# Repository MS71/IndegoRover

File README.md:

# IndegoRover
new MainBoard for Indego Lawn Mower

Prototype:

Schematic:
https://github.com/MS71/IndegoRover/blob/main/kicad/IndegoMower/pdf/IndegoMower.pdf

PCB:

Parts:
* ESP32 (S2/S3) Module (https://github.com/MS71/ROS2Mower/blob/master/hw/esp32_module.pdf)
* ARV Mega 128 for low level IO, security and motor driver
* origonal Indego connectors (26SHC-B-1A => mouser)
* DC motor driver: 3 * VNH2SP30 module (41V, 30A H Bridge)
* GPS receiver (ZED-F9P) (https://www.ardusimple.com/product/simplertk2blite/)
* 5 pin header for low cost, non RTK GPS receiver
* 10 Pin RPI Connector (5V, 3.3V, GND, I2C, UART)
* 10 Pin I2C Bus Connector
* 6 Pin I2C Bus Connector
* 5V Step Down Converter
* Bat Charger Circuit (Compatible with Indego Charge Station, difficult)
* Bat Charger Circuit (Compatible with std. 36V solar panel)
* Coil Sensor Amp
* low power + standby
* support for all available sensors
* BNO055 IMU module headers
* support for all sensors (bumper, coil fensem ...)
* power supply for onboard computer
* beeper
* support for LCD and keyboard (difficult)
* some breadboard area for custom extensions
* ...

onboard ROS2 computer: (optional)
* RPI4 or RPI Zero 2W headers 
* Orange Pi Zero 2 headers (http://www.orangepi.org/Orange%20Pi%20Zero2/)
* ...

Other:
* made with free Eagle  (max. 80 qcm) or kicad6

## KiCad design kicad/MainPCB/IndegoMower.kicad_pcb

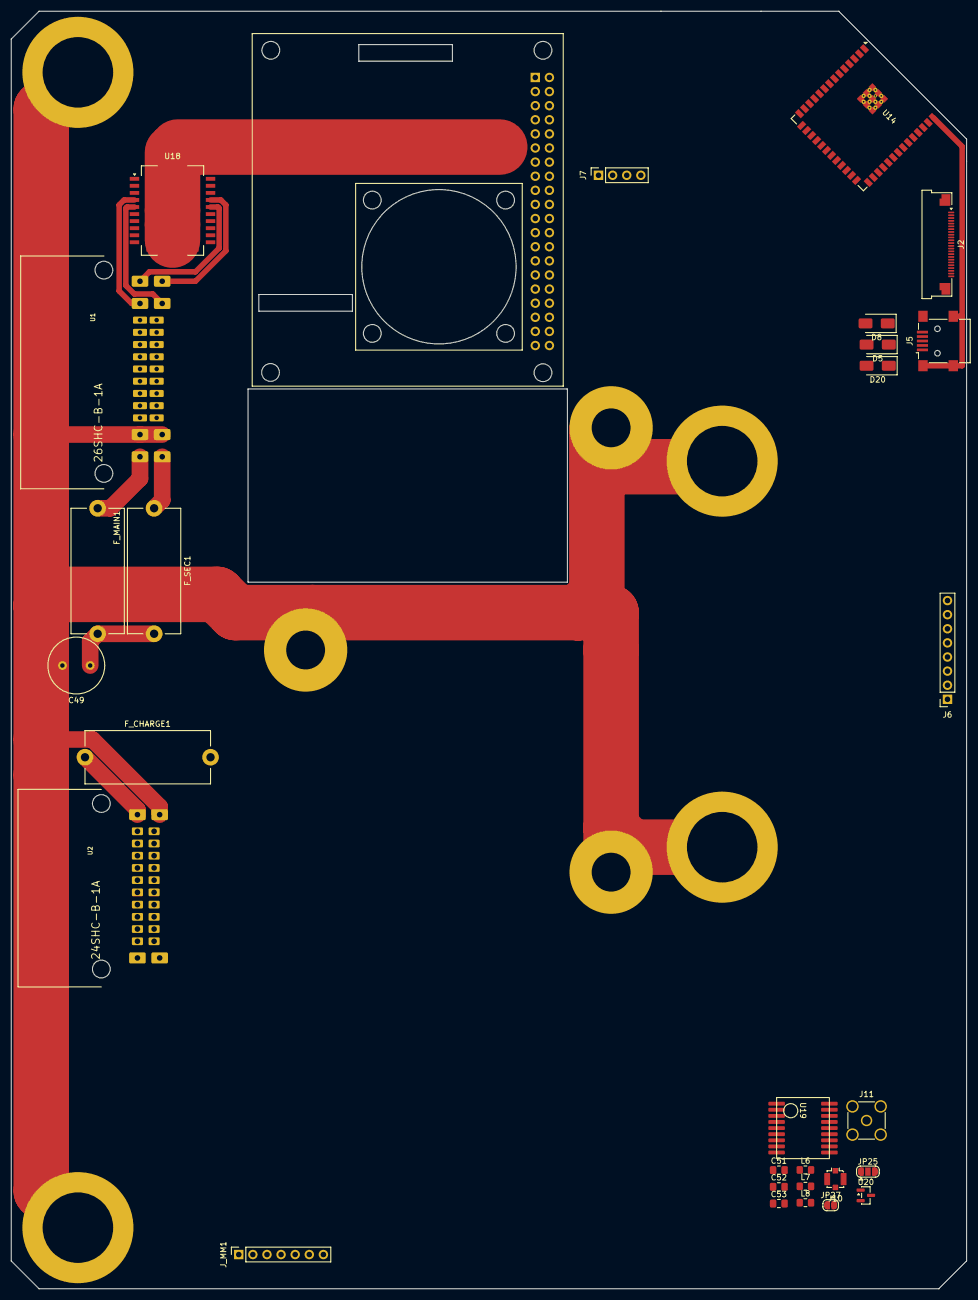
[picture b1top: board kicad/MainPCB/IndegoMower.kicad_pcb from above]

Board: 2 copper layers, 172.0 x 230.0 mm, 29 parts (1 on the bottom side), 38 nets.

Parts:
C49: 680uF / 63V; C_Radial_D10.0mm_H16.0mm_P5.00mm
C51, C52, C53: 100nF; C_0805_2012Metric_Pad1.18x1.45mm_HandSolder
D5, D8, D20: P4SMAJ5.0CA; D_SMA
F_CHARGE1: 4A; Fuseholder_Cylinder-5x20mm_Stelvio-Kontek_PTF78_Horizontal_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
F_MAIN1: 6A; Fuseholder_Cylinder-5x20mm_Stelvio-Kontek_PTF78_Horizontal_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
F_SEC1: 6A; Fuseholder_Cylinder-5x20mm_Stelvio-Kontek_PTF78_Horizontal_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
J1: RPi_GPIO; PinSocket_2x20_P2.54mm_Vertical
J2: Conn_01x24_FFC_0.5mm_AFC01-S24FCC-00; Amphenol_F32R-1A7x1-11024_1x24-1MP_P0.5mm_Horizontal
J5: USB_OTG; USB_Mini-B_Lumberg_2486_01_Horizontal
J6: BNO055; PinSocket_1x08_P2.54mm_Vertical
J7: OLED; PinSocket_1x04_P2.54mm_Vertical
J10: IPEX; U.FL_Molex_MCRF_73412-0110_Vertical
J11: SMA; SMA_Amphenol_132134-11_Vertical
JP25: SolderJumper_3_Open; SolderJumper-3_P1.3mm_Open_RoundedPad1.0x1.5mm
JP27: SolderJumper_2_Open; SolderJumper-2_P1.3mm_Open_RoundedPad1.0x1.5mm
J_MM1: PinSocket_1x07_P2.54mm_Vertical
L6: 1.2uH; L_0805_2012Metric_Pad1.15x1.40mm_HandSolder
L7, L8: 39nH; L_0805_2012Metric_Pad1.15x1.40mm_HandSolder
U1: 26SHC-B-1A
U2: 24SHC-B-1A
U14: ESP32-S3-WROOM-2 (-1); ESP32-S3-WROOM-2
U18: L298P; HSOP-20-1EP_11.0x15.9mm_P1.27mm_SlugDown
U19: RTK-1010; rtk1010
U20: MCP1700-3302E_SOT23; SOT-23

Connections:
+2V8: J2.14, J2.21
+3.3V: J_MM1.7, U18.12 (Vss)
CAM_D0: J2.6, U14.23 (GPIO21)
CAM_D1: J2.4, U14.39 (GPIO1/TOUCH1/ADC1_CH0)
CAM_D2: J2.3, U14.38 (GPIO2/TOUCH2/ADC1_CH1)
CAM_D3: J2.5, U14.35 (MTMS/GPIO42)
CAM_D4: J2.7, U14.34 (MTDI/GPIO41/CLK_OUT1)
CAM_D5: J2.9, U14.33 (MTDO/GPIO40/CLK_OUT2)
CAM_D6: J2.11, U14.32 (MTCK/GPIO39/CLK_OUT3/SUBSPICS1)
CAM_D7: J2.13, U14.31 (GPIO38/FSPIWP/SUBSPIWP)
CAM_HREF: J2.16, U14.25 (GPIO48/SPICLK_N/SUBSPICLK_N_DIFF)
CAM_PCLK: J2.8, U14.26 (GPIO45)
CAM_SDA: J2.22, U14.4 (GPIO4/TOUCH4/ADC1_CH3)
CAM_XCLK: J2.12, U14.16 (GPIO46)
GND: C51.2, C52.2, C53.2, J2.10, J2.23, J10.2 (Ext), J11.2 (Ext), U19.1 (GND1), U19.10 (GND10), U19.12 (GND12), U20.1 (GND)
GNDD: C49.2, D5.2 (A2), D8.2 (A2), D20.2 (A2), J5.5 (GND), J5.6 (Shield), J_MM1.6, U1.P$8, U1.P$14, U1.P$24, U1.P$25, U2.P$3, U2.P$21, U14.1 (GND), U14.40 (GND), U14.41 (GND)
GNDPWR: J1.6 (GND), J1.9 (GND), J1.14 (GND), J1.20 (GND), J1.25 (GND), J1.30 (GND), J1.34 (GND), J1.39 (GND), U18.1 (GND), U18.10 (GND), U18.11 (GND), U18.20 (GND)
ML_N: U1.P$5, U18.5 (OUT2)
ML_P: U1.P$4, U18.4 (OUT1)
MR_N: U1.P$3, U18.17 (OUT4)
MR_P: U1.P$2, U18.16 (OUT3)
unnamed: D5.1 (A1), J5.2 (D-)
unnamed: D8.1 (A1), J5.3 (D+)
unnamed: D20.1 (A1), J5.4 (ID)
unnamed: J10.1 (In), J11.1 (In), L7.2, L8.2, U19.11 (RF_IN)
unnamed: C51.1, JP25.1 (A), JP27.1 (A), L6.2, U19.8 (VCC)
unnamed: JP25.2 (C), U19.6 (V_BKUP)
unnamed: JP27.2 (B), U19.7 (NC7)
unnamed: F_MAIN1.1, U1.P$26
unnamed: F_SEC1.1, U1.P$27
unnamed: F_CHARGE1.1, U2.P$2
unnamed: L8.1, U19.14 (VCC_RF)
U5: C52.1, U20.3 (VI)
U5SW: U1.P$9, U1.P$15, U2.P$20
UB: C49.1, F_MAIN1.2, F_SEC1.2
ULNA: C53.1, L7.1, U20.2 (VO)
U_55: J1.2 (5V), J1.4 (5V)
VCC_STBY: JP25.3 (B), U14.2 (3V3)

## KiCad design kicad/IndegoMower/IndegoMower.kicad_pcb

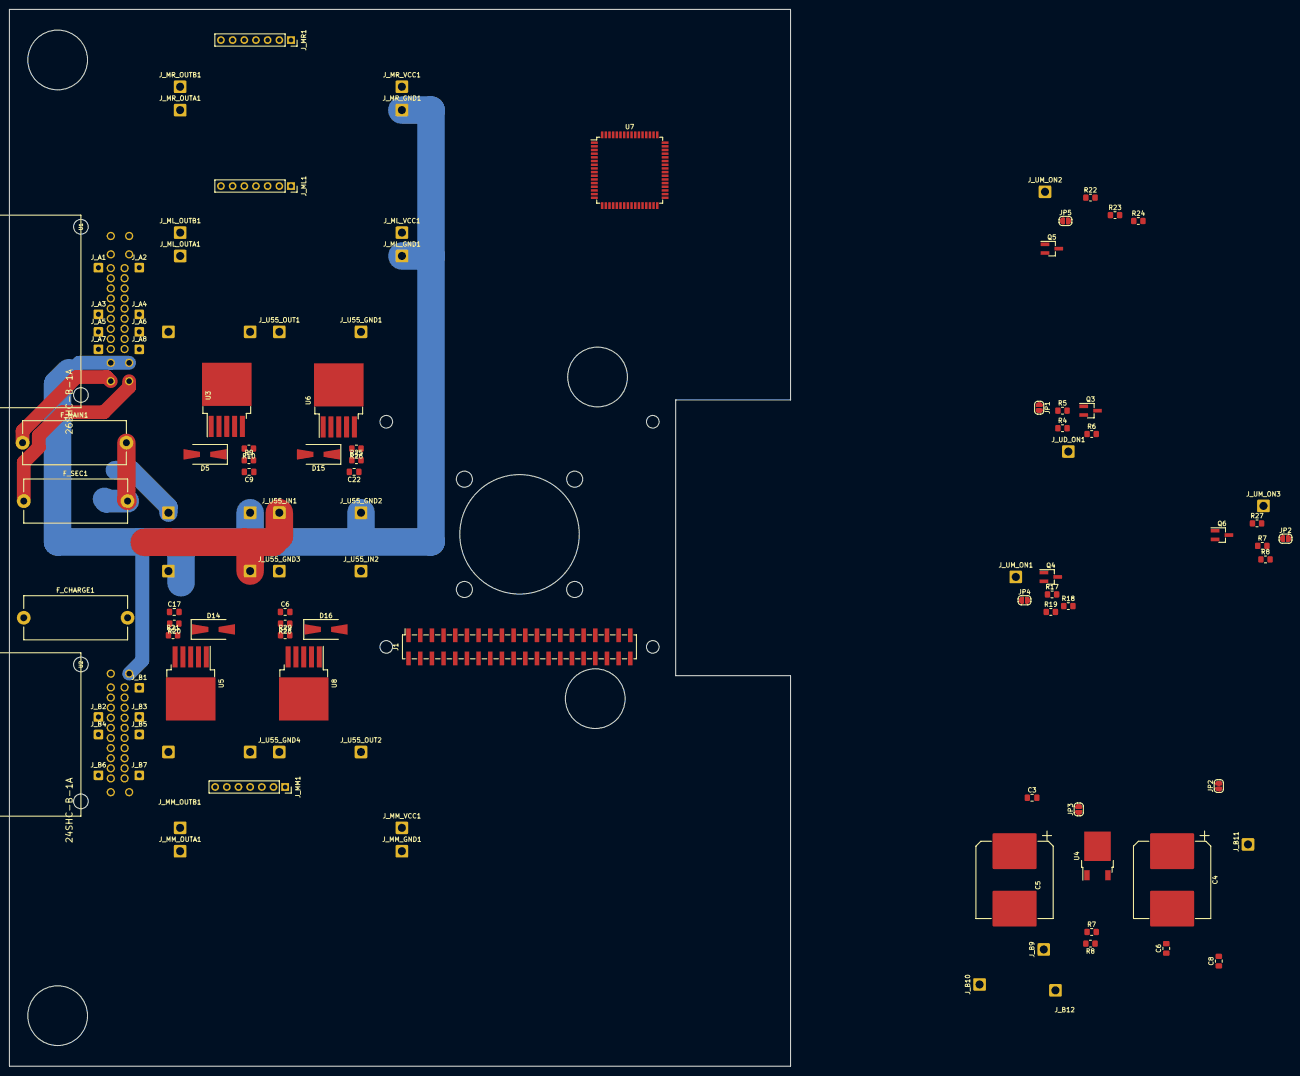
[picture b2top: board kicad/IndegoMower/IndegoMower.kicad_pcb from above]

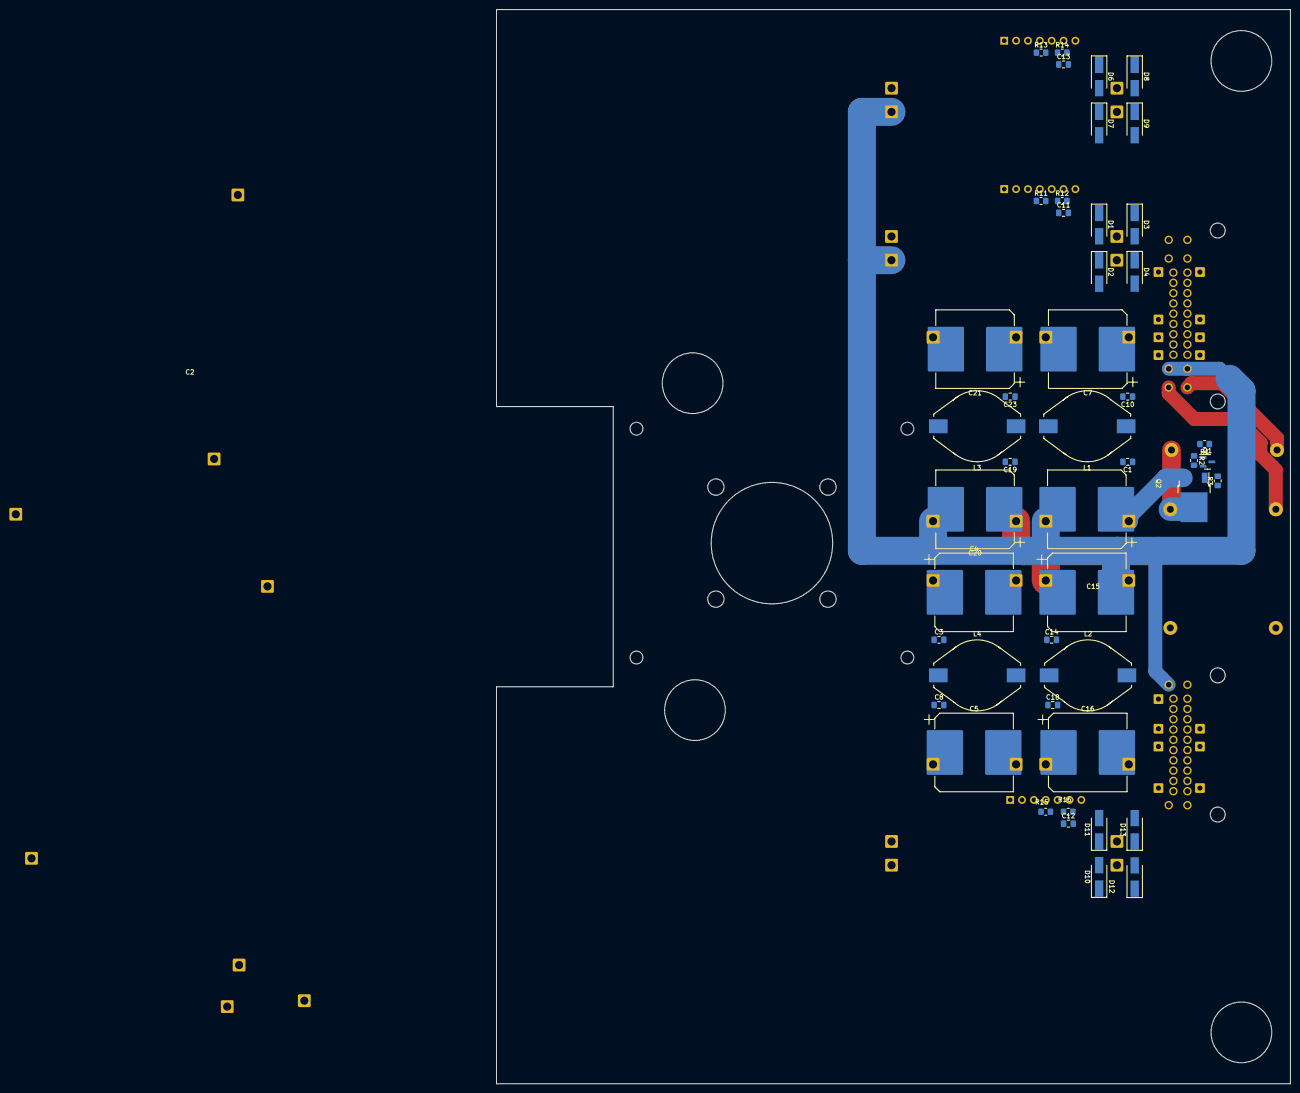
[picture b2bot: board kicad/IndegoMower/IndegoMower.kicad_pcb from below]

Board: 2 copper layers, 170.0 x 230.0 mm, 157 parts (46 on the bottom side), 61 nets.

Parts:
C1, C3, C6, C8, C10: 0.1; C_0805_2012Metric_Pad1.18x1.45mm_HandSolder
C2: 680uF/50V; CP_Elec_16x17.5
C3#2, C6#2, C8#2, C11, C12, C13, C14, C17, C18, C19, C22, C23: C_0805_2012Metric_Pad1.18x1.45mm_HandSolder
C4, C4#2, C5, C5#2, C15, C16, C20, C21: CP_Elec_16x17.5
C7: 220uF/40V; CP_Elec_16x17.5
C9: 560pF; C_0805_2012Metric_Pad1.18x1.45mm_HandSolder
D1, D2, D3, D4, D6, D7, D8, D9, D10, D11, D12, D13: D_SMA_Handsoldering
D5, D14, D15, D16: D_SMA-SMB_Universal_Handsoldering
F_CHARGE1: 4A; Fuseholder_Cylinder-5x20mm_Stelvio-Kontek_PTF78_Horizontal_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
F_MAIN1: 6A; Fuseholder_Cylinder-5x20mm_Stelvio-Kontek_PTF78_Horizontal_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
F_SEC1: 6A; Fuseholder_Cylinder-5x20mm_Stelvio-Kontek_PTF78_Horizontal_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
J1: RPi_GPIO; PinSocket_2x20_P2.54mm_Vertical_SMD
JP1, JP2#2: SolderJumper_2_Open; SolderJumper-2_P1.3mm_Open_RoundedPad1.0x1.5mm
JP2, JP3, JP4, JP5: SolderJumper-2_P1.3mm_Open_RoundedPad1.0x1.5mm
J_A1: Conn_01x01_Female; SolderWire-0.5sqmm_1x01_D0.9mm_OD2.1mm
J_A2, J_A3, J_A4, J_A5, J_A6, J_A7, J_A8: SolderWire-0.5sqmm_1x01_D0.9mm_OD2.1mm
J_B1, J_B2, J_B3, J_B4, J_B5, J_B6, J_B7: SolderWire-0.5sqmm_1x01_D0.9mm_OD2.1mm
J_B9, J_B10, J_B11, J_B12: SolderWire-1sqmm_1x01_D1.4mm_OD2.7mm
J_ML1: Conn_01x07; PinSocket_1x07_P2.54mm_Vertical
J_ML_GND1: SolderWire-1sqmm_1x01_D1.4mm_OD2.7mm
J_ML_OUTA1: SolderWire-1sqmm_1x01_D1.4mm_OD2.7mm
J_ML_OUTB1: SolderWire-1sqmm_1x01_D1.4mm_OD2.7mm
J_ML_VCC1: SolderWire-1sqmm_1x01_D1.4mm_OD2.7mm
J_MM1: PinSocket_1x07_P2.54mm_Vertical
J_MM_GND1: SolderWire-1sqmm_1x01_D1.4mm_OD2.7mm
J_MM_OUTA1: SolderWire-1sqmm_1x01_D1.4mm_OD2.7mm
J_MM_OUTB1: SolderWire-1sqmm_1x01_D1.4mm_OD2.7mm
J_MM_VCC1: SolderWire-1sqmm_1x01_D1.4mm_OD2.7mm
J_MR1: PinSocket_1x07_P2.54mm_Vertical
J_MR_GND1: SolderWire-1sqmm_1x01_D1.4mm_OD2.7mm
J_MR_OUTA1: SolderWire-1sqmm_1x01_D1.4mm_OD2.7mm
J_MR_OUTB1: SolderWire-1sqmm_1x01_D1.4mm_OD2.7mm
J_MR_VCC1: SolderWire-1sqmm_1x01_D1.4mm_OD2.7mm
J_U55_GND1, J_U55_GND2, J_U55_GND3, J_U55_GND4, J_U55_IN1, J_U55_IN2, J_U55_OUT1, J_U55_OUT2: SolderWire-1sqmm_1x01_D1.4mm_OD2.7mm
J_UD_GND1, J_UD_GND2: SolderWire-1sqmm_1x01_D1.4mm_OD2.7mm
J_UD_IN1: SolderWire-1sqmm_1x01_D1.4mm_OD2.7mm
J_UD_ON1: SolderWire-1sqmm_1x01_D1.4mm_OD2.7mm
J_UD_OUT1: SolderWire-1sqmm_1x01_D1.4mm_OD2.7mm
J_UM_GND1, J_UM_GND2: SolderWire-1sqmm_1x01_D1.4mm_OD2.7mm
J_UM_IN1: SolderWire-1sqmm_1x01_D1.4mm_OD2.7mm
J_UM_ON1, J_UM_ON2, J_UM_ON3: SolderWire-1sqmm_1x01_D1.4mm_OD2.7mm
J_UM_OUT1: SolderWire-1sqmm_1x01_D1.4mm_OD2.7mm
L1, L2, L3, L4: 33uH; L_Fastron_PISR_Handsoldering
Q1: BC847; SOT-23
Q2: TSM480P06CP; TO-252-2
Q3: BC847; SOT-23_Handsoldering
Q4, Q5, Q6: SOT-23_Handsoldering
R1, R4: 10k; R_0805_2012Metric_Pad1.20x1.40mm_HandSolder
R2, R5: 47k; R_0805_2012Metric_Pad1.20x1.40mm_HandSolder
R3: 330k; R_0805_2012Metric_Pad1.20x1.40mm_HandSolder
R6: 100k; R_0805_2012Metric_Pad1.20x1.40mm_HandSolder
R7, R7#2, R8, R8#2, R9, R10, R11, R12, R13, R14, R15, R16, R17, R18, R19, R20, R21, R22, R23, R24, R25, R26, R27, R28, R29: R_0805_2012Metric_Pad1.20x1.40mm_HandSolder
U1: 26SHC-B-1A
U2: 24SHC-B-1A
U3: LM2596S-ADJ; TO-263-5_TabPin3
U4: LM317_TO-252; TO-252-2
U5, U6, U8: TO-263-5_TabPin3
U7: ATmega128A-A; TQFP-64_14x14mm_P0.8mm

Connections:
GNDD: C11.2, C12.2, C13.2, J_ML1.6, J_MM1.6, J_MR1.6, Q1.2 (E), R2.2, R12.2, R14.2, R16.2, U1.P$8, U2.P$21, U7.22 (GND), U7.53 (GND), U7.63 (GND)
GNDPWR: C1.2, C2.2, C3.2, C3#2.2, C4.2, C4#2.2, C5.2, C5#2.2, C6.2, C7.2, C8.2, C8#2.2, C10.2, C14.2, C15.2, C16.2, C18.2, C19.2, C20.2, C21.2, C23.2, D2.2 (A), D4.2 (A), D5.2 (A), D7.2 (A), D9.2 (A), D11.2 (A), D13.2 (A), D14.2 (A), D15.2 (A), D16.2 (A), J1.6 (GND), J1.9 (GND), J1.14 (GND), J1.20 (GND), J1.25 (GND), J1.30 (GND), J1.34 (GND), J1.39 (GND), J_B9.1, J_B10.1, J_ML_GND1.1, J_MM_GND1.1, J_MR_GND1.1, J_U55_GND1.1, J_U55_GND2.1, J_U55_GND3.1, J_U55_GND4.1, J_UD_GND1.1, J_UD_GND2.1, J_UM_GND1.1, J_UM_GND2.1, Q3.2 (E), Q4.2 (E), Q5.2 (E), Q6.2 (E), R5.2, R8.2, R8#2.2, R10.2, R18.2, R21.2, R23.2, R26.2, R29.2, U1.P$24, U1.P$25, U2.P$3, U3.3 (GND), U5.3 (GND), U6.3 (GND), U8.3 (GND)
ML_CS: C11.1, R11.2, R12.1
ML_N: D1.2 (A), D2.1 (K), J_ML_OUTB1.1, U1.P$5
ML_P: D3.2 (A), D4.1 (K), J_ML_OUTA1.1, U1.P$4
MM_CS: C13.1, R15.2, R16.1
MM_N: D10.2 (A), D11.1 (K), J_MM_OUTB1.1, U2.P$25
MM_P: D12.2 (A), D13.1 (K), J_MM_OUTA1.1, U2.P$24
MR_CS: C12.1, R13.2, R14.1
MR_N: D6.2 (A), D7.1 (K), J_MR_OUTB1.1, U1.P$3
MR_P: D8.2 (A), D9.1 (K), J_MR_OUTA1.1, U1.P$2
M_VCC: J_ML1.7, J_MM1.7, J_MR1.7
unnamed: C5.1, C6.1, JP2#2.1 (A), JP3.2 (B), J_B11.1, R7#2.1, U4.2 (VO)
unnamed: C6#2.1, R28.2, R29.1, U8.4 (FB)
unnamed: C9.1, R9.2, R10.1, U3.4 (FB)
unnamed: C17.1, R20.2, R21.1, U5.4 (FB)
unnamed: C22.1, R25.2, R26.1, U6.4 (FB)
unnamed: D5.1 (K), L1.1, U3.2 (OUT)
unnamed: D14.1 (K), L2.1, U5.2 (OUT)
unnamed: D15.1 (K), L3.1, U6.2 (OUT)
unnamed: D16.1 (K), L4.1, U8.2 (OUT)
unnamed: F_CHARGE1.1, U2.P$2
unnamed: F_MAIN1.1, U1.P$26
unnamed: F_SEC1.1, U1.P$27
unnamed: JP1.1 (A), Q3.1 (B), R4.1, R5.1
unnamed: JP1.2 (B), J_UD_ON1.1, Q3.3 (C), R6.2, U3.5 (~ON/OFF)
unnamed: JP2.1 (A), Q6.1 (B), R7.1, R8#2.1
unnamed: JP2.2 (B), J_UM_ON3.1, Q6.3 (C), R27.2, U8.5 (~ON/OFF)
unnamed: JP4.1 (A), Q4.1 (B), R17.1, R18.1
unnamed: JP4.2 (B), J_UM_ON1.1, Q4.3 (C), R19.2, U5.5 (~ON/OFF)
unnamed: JP5.1 (A), Q5.1 (B), R22.1, R23.1
unnamed: JP5.2 (B), J_UM_ON2.1, Q5.3 (C), R24.2, U6.5 (~ON/OFF)
unnamed: J_A1.1, U1.P$6
unnamed: J_A2.1, U1.P$7
unnamed: J_A3.1, U1.P$16
unnamed: J_A4.1, U1.P$17
unnamed: J_A5.1, U1.P$18
unnamed: J_A6.1, U1.P$19
unnamed: J_A7.1, U1.P$20
unnamed: J_A8.1, U1.P$21
unnamed: J_B1.1, U2.P$5
unnamed: J_B2.1, U2.P$10
unnamed: J_B3.1, U2.P$11
unnamed: J_B4.1, U2.P$14
unnamed: J_B5.1, U2.P$15
unnamed: J_B6.1, U2.P$22
unnamed: J_B7.1, U2.P$23
unnamed: J_ML1.4, R11.1
unnamed: J_MM1.4, R15.1
unnamed: J_MR1.4, R13.1
unnamed: Q1.1 (B), R1.1, R2.1
unnamed: Q1.3 (C), Q2.1 (G), R3.2
unnamed: R7#2.2, R8.1, U4.1 (ADJ)
ON_U24: R4.2, R7.2, R17.2, R22.2
U5SW: U1.P$9, U2.P$20
UB: C3.1, C4.1, F_MAIN1.2, F_SEC1.2, JP3.1 (A), Q2.2 (D), R3.1, U4.3 (VI)
U_55: C5#2.1, C6#2.2, C8#2.1, C21.1, C22.2, C23.1, J1.2 (5V), J1.4 (5V), J_U55_OUT1.1, J_U55_OUT2.1, L3.2, L4.2, R25.1, R28.1
U_BAT_SW: C1.1, C2.1, C3#2.1, C4#2.1, C14.1, C15.1, C19.1, C20.1, J_U55_IN1.1, J_U55_IN2.1, J_UD_IN1.1, J_UM_IN1.1, Q2.3 (S), R6.1, R19.1, R24.1, R27.1, U3.1 (VIN), U5.1 (VIN), U6.1 (VIN), U8.1 (VIN)
U_DRIVE: C7.1, C9.2, C10.1, D1.1 (K), D3.1 (K), D6.1 (K), D8.1 (K), J_ML_VCC1.1, J_MR_VCC1.1, J_UD_OUT1.1, L1.2, R9.1
U_MOWER: C16.1, C17.2, C18.1, D10.1 (K), D12.1 (K), J_MM_VCC1.1, J_UM_OUT1.1, L2.2, R20.1
VCC: C8.1, JP2#2.2 (B), J_B12.1, U7.21 (VCC), U7.52 (VCC)

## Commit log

2022-03-21 added
2022-05-18 new kicad pcb added
2022-06-05 some more work
2022-06-05 pdf added
2022-06-05 3D image added
2022-06-15 rtk1010 board added
2022-06-15 rtk1010 board updated
2022-06-18 some optimiziations
2025-10-19 project restart 2025
2025-10-21 some further progress
2025-10-22 some work ...
2025-11-19 some more changes
